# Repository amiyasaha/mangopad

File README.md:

# mangopad

mangopad is a 9-key macropad with a Rotary Encoder, and an OLED screen. It was made as part of Hack Club's Highway YSWS. [Here](https://youtube.com/shorts/6rCVxwxAsbE)'s a link to the Demo!

# CAD
The case was designed in Fusion 360 and has 3 compartments: the top case, the plate, and the bottom case.

# PCB
The PCB was designed in KiCAD 

# Firmware
The firmware was written in Python, using the KMK library.

# BOM
- 9x Cherry MX Switches
- 9x DSA Keycaps
- 9x 1N148 Diodes22222
- 4x M3x5x4 Heatset Inserts
- 4x M3x16mm Screws
- 1x 0.91" 128x32 SSD1306 OLED Display
- 1x EC11 Rotary Encoder
- 1x XIAO RP2040
- 3D Printed Top, Plate, and Bottom

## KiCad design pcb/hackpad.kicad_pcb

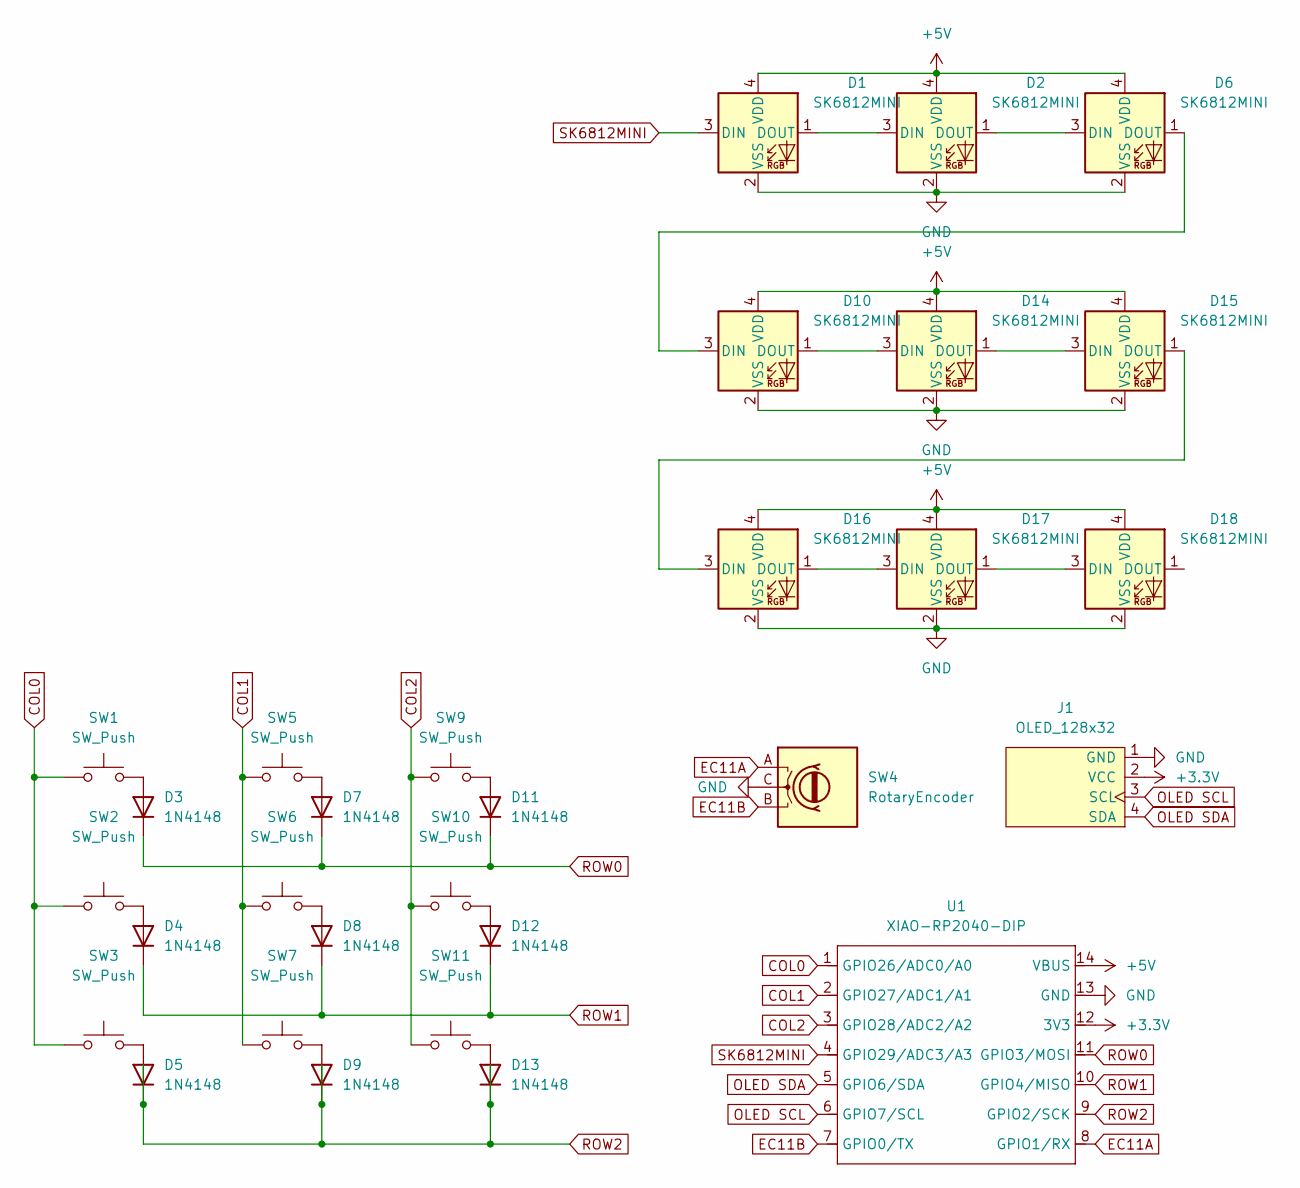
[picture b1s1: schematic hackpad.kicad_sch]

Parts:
D1, D2, D6, D10, D14, D15, D16, D17, D18: SK6812MINI; LED_SK6812MINI_PLCC4_3.5x3.5mm_P1.75mm
D3, D4, D5, D7, D8, D9, D11, D12, D13: 1N4148; D_DO-35_SOD27_P7.62mm_Horizontal
J1: OLED_128x32; SSD1306-0.91-OLED-4pin-128x32
SW1, SW2, SW3, SW5, SW6, SW7, SW9, SW10, SW11: SW_Push; SW_Cherry_MX_1.00u_PCB
SW4: RotaryEncoder; RotaryEncoder_Alps_EC11E_Vertical_H20mm
U1: XIAO-RP2040-DIP

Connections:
+3.3V: J1.2 (VCC), U1.12 (3V3)
+5V: D1.4 (VDD), D2.4 (VDD), D6.4 (VDD), D10.4 (VDD), D14.4 (VDD), D15.4 (VDD), D16.4 (VDD), D17.4 (VDD), D18.4 (VDD), U1.14 (VBUS)
COL0: SW1.1, SW2.1, SW3.1, U1.1 (GPIO26/ADC0/A0)
COL1: SW5.1, SW6.1, SW7.1, U1.2 (GPIO27/ADC1/A1)
COL2: SW9.1, SW10.1, SW11.1, U1.3 (GPIO28/ADC2/A2)
EC11A: SW4.A, U1.8 (GPIO1/RX)
EC11B: SW4.B, U1.7 (GPIO0/TX)
GND: D1.2 (VSS), D2.2 (VSS), D6.2 (VSS), D10.2 (VSS), D14.2 (VSS), D15.2 (VSS), D16.2 (VSS), D17.2 (VSS), D18.2 (VSS), J1.1 (GND), SW4.C, U1.13 (GND)
unnamed: D1.1 (DOUT), D2.3 (DIN)
unnamed: D2.1 (DOUT), D6.3 (DIN)
unnamed: D3.2 (A), SW1.2
unnamed: D4.2 (A), SW2.2
unnamed: D5.2 (A), SW3.2
unnamed: D7.2 (A), SW5.2
unnamed: D8.2 (A), SW6.2
unnamed: D9.2 (A), SW7.2
unnamed: D6.1 (DOUT), D10.3 (DIN)
unnamed: D10.1 (DOUT), D14.3 (DIN)
unnamed: D11.2 (A), SW9.2
unnamed: D12.2 (A), SW10.2
unnamed: D13.2 (A), SW11.2
unnamed: D14.1 (DOUT), D15.3 (DIN)
unnamed: D15.1 (DOUT), D16.3 (DIN)
unnamed: D16.1 (DOUT), D17.3 (DIN)
unnamed: D17.1 (DOUT), D18.3 (DIN)
OLED SCL: J1.3 (SCL), U1.6 (GPIO7/SCL)
OLED SDA: J1.4 (SDA), U1.5 (GPIO6/SDA)
ROW0: D3.1 (K), D7.1 (K), D11.1 (K), U1.11 (GPIO3/MOSI)
ROW1: D4.1 (K), D8.1 (K), D12.1 (K), U1.10 (GPIO4/MISO)
ROW2: D5.1 (K), D9.1 (K), D13.1 (K), U1.9 (GPIO2/SCK)
SK6812MINI: D1.3 (DIN), U1.4 (GPIO29/ADC3/A3)

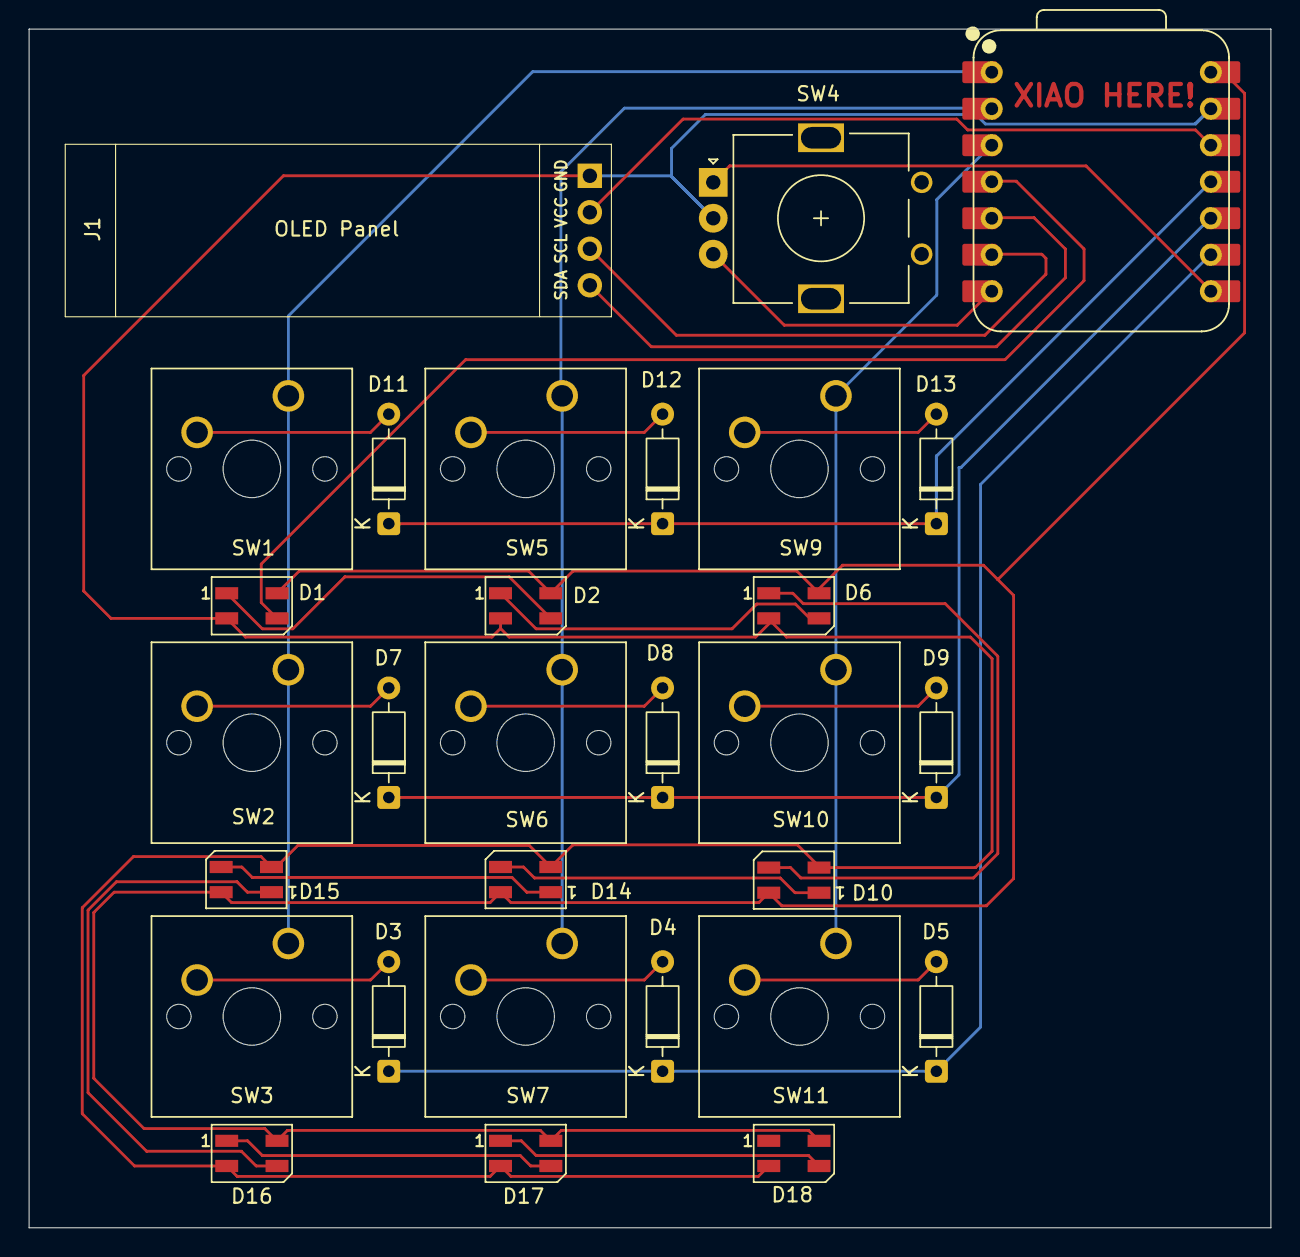
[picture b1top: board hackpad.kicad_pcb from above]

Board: 2 copper layers, 86.4 x 83.4 mm, 30 parts (0 on the bottom side), 31 nets.

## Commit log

2025-07-08 readme added
2025-07-09 added cad, pcbs, firmware, and prod files
2025-07-09 updated firmware
2025-08-15 updated files
2025-08-15 bad stuff gone
